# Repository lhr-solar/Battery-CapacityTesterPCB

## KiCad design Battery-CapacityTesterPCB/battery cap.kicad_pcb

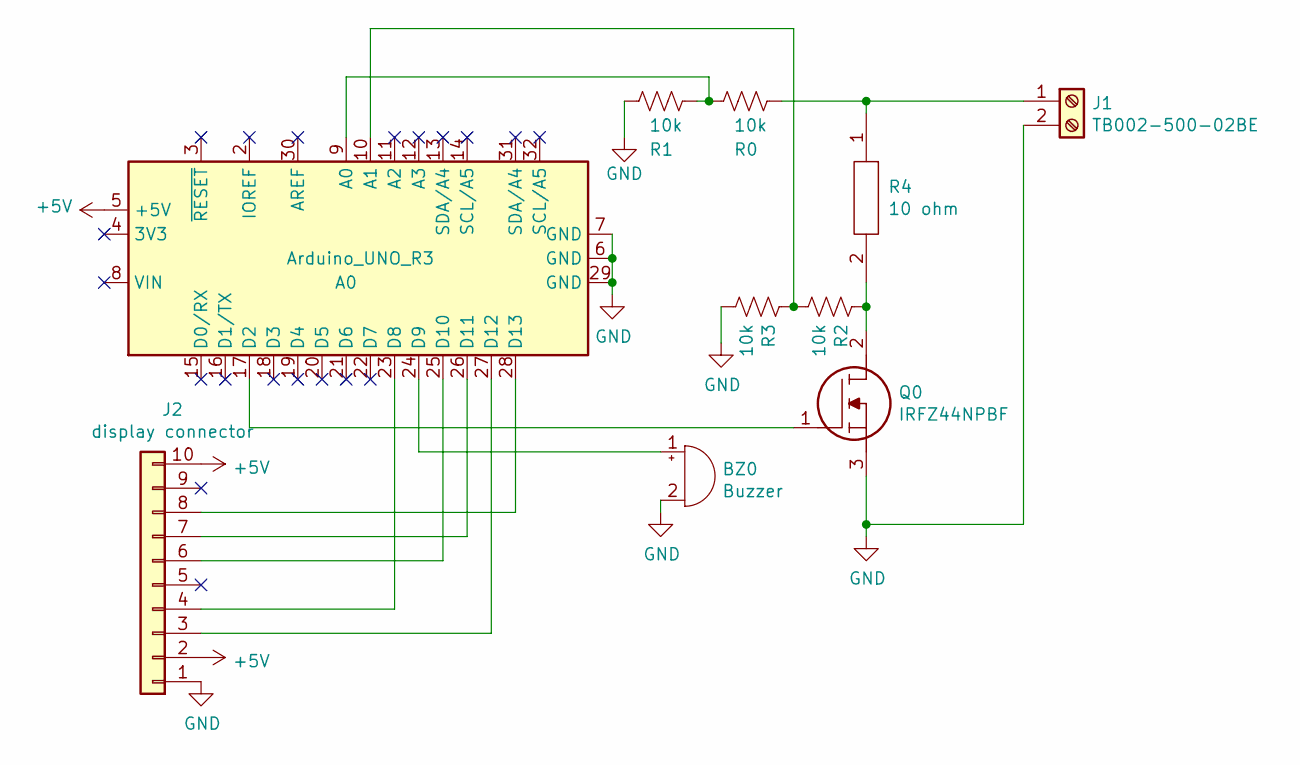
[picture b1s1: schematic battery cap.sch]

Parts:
A0: Arduino_UNO_R3
BZ0: Buzzer; MagneticBuzzer_ProSignal_ABT-410-RC
J1: TB002-500-02BE; SHDR2W100P0X500_1X2_1000X760X1040P; Mouser Part Number 490-TB002-500-02BE
J2: display connector; PinHeader_1x10_P2.54mm_Vertical
Q0: IRFZ44NPBF; TO254P483X1016X1994-3P; Mouser Part Number 942-IRFZ44NPBF
R0, R1, R2, R3: 10k; R_0805_2012Metric_Pad1.15x1.40mm_HandSolder
R4: 10 ohm; RESAD8570W94L4762D952; Mouser Part Number 71-CP001010R00JE14

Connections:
+5V: A0.5 (+5V), J2.2, J2.10
GND: A0.6 (GND), A0.7 (GND), A0.29 (GND), BZ0.2 (+), J1.2, J2.1, Q0.3, R1.2, R3.2
unnamed: A0.9 (A0), R0.2, R1.1
unnamed: A0.10 (A1), R2.2, R3.1
unnamed: A0.17 (D2), Q0.1
unnamed: A0.23 (D8), J2.4
unnamed: A0.24 (D9), BZ0.1 (-)
unnamed: A0.25 (D10), J2.6
unnamed: A0.26 (D11), J2.7
unnamed: A0.27 (D12), J2.3
unnamed: A0.28 (D13), J2.8
unnamed: J1.1, R0.1, R4.1
unnamed: Q0.2, R2.1, R4.2

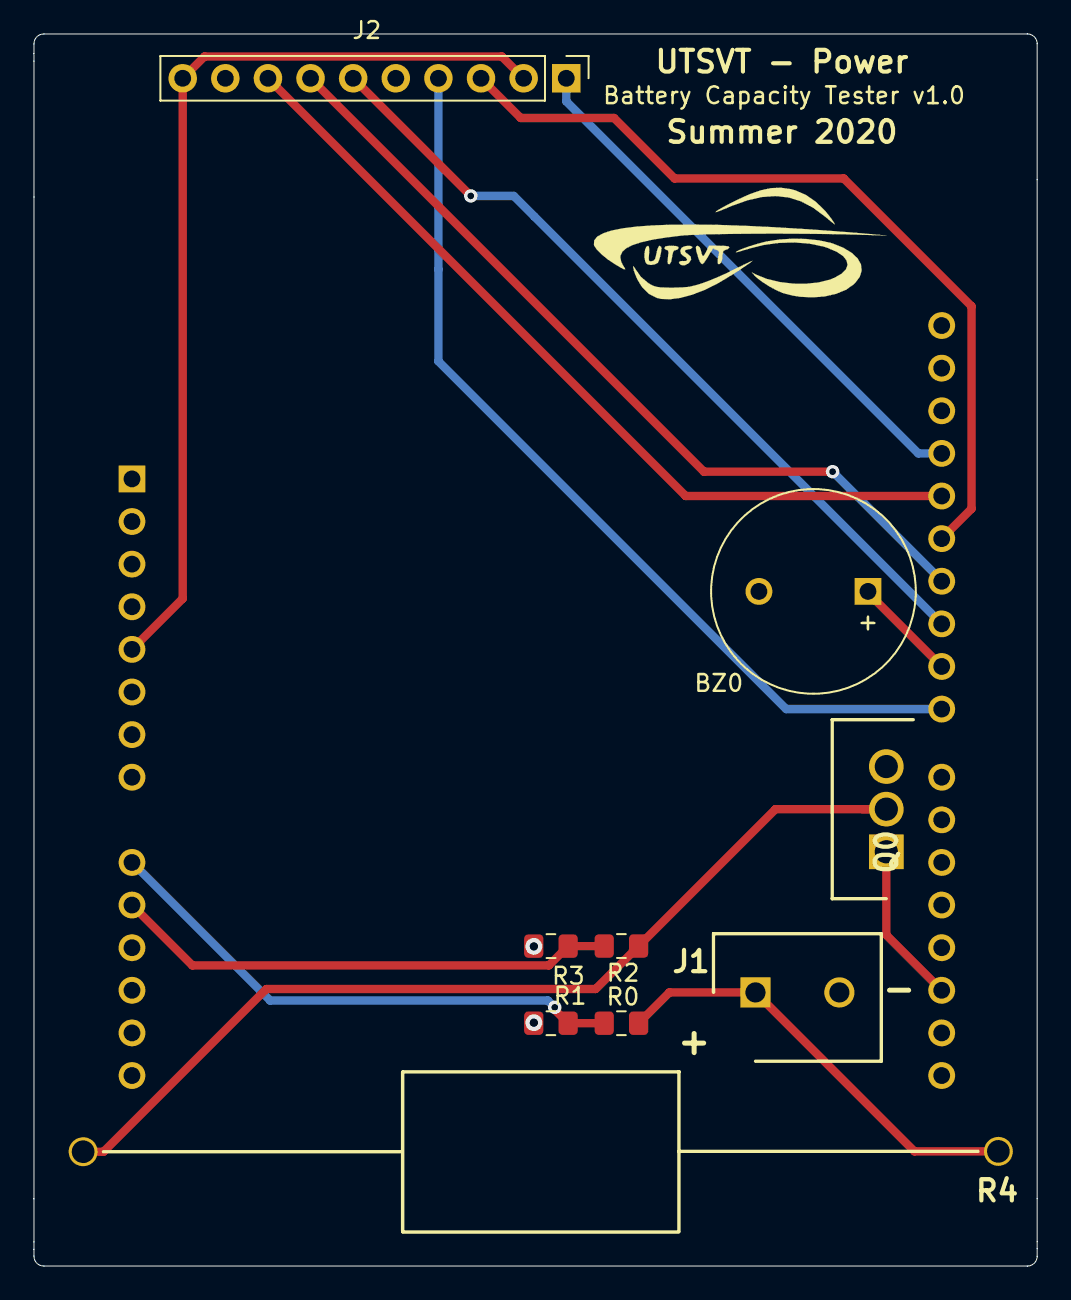
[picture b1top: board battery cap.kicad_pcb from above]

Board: 2 copper layers, 59.8 x 73.4 mm, 10 parts (1 on the bottom side), 13 nets.

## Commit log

2020-10-03 Adds QuAC
2020-10-03 Creates gerbers for release and deletes them
2020-10-03 Add files via upload (#1)
    * Add files via upload
    * Creates gerbers for release and deletes them
